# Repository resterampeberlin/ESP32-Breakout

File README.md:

# Purpose

# Credits

This open source code project is has been proudfully produced in Berlin (and other places around the globe) by

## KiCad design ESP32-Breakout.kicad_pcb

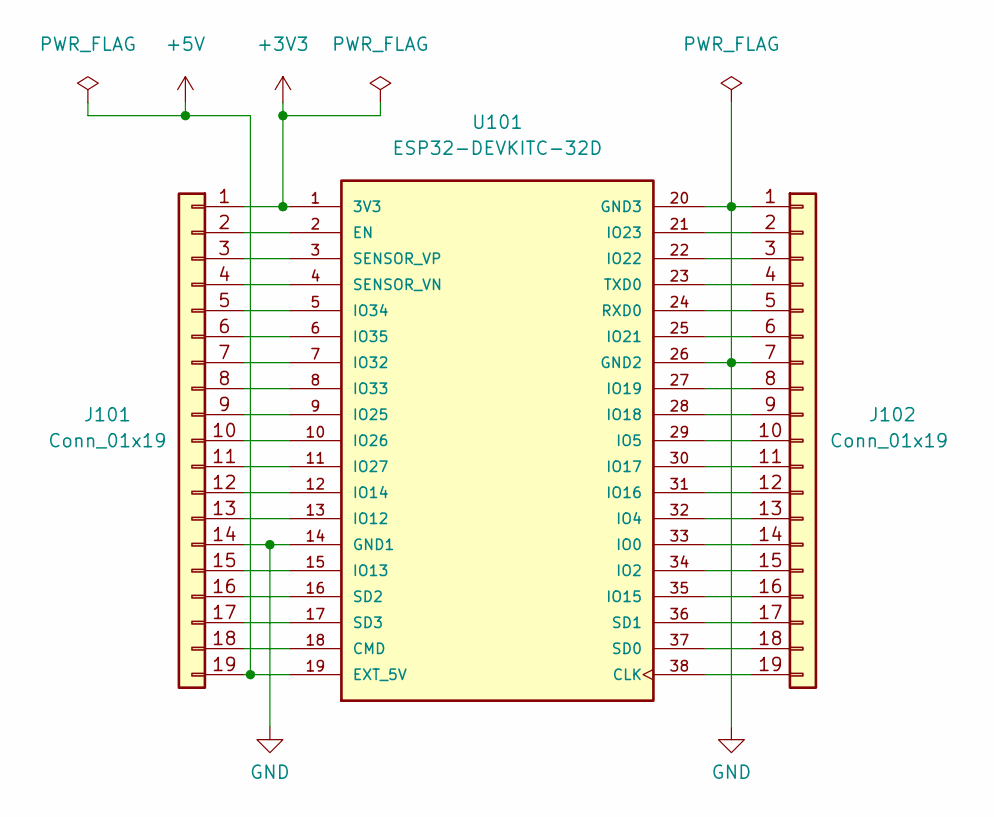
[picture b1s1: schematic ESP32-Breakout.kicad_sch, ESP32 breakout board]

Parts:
J101, J102: Conn_01x19; PinHeader_1x19_P2.54mm_Vertical
U101: ESP32-DEVKITC-32D; MODULE_ESP32-DEVKITC-32D_Stacking_header_TH; PARTREV 4

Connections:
+3V3: J101.1, U101.1 (3V3)
+5V: J101.19, U101.19 (EXT_5V)
GND: J101.14, J102.1, J102.7, U101.14 (GND1), U101.20 (GND3), U101.26 (GND2)
unnamed: J102.2, U101.21 (IO23)
unnamed: J102.3, U101.22 (IO22)
unnamed: J102.4, U101.23 (TXD0)
unnamed: J102.5, U101.24 (RXD0)
unnamed: J102.6, U101.25 (IO21)
unnamed: J102.8, U101.27 (IO19)
unnamed: J102.9, U101.28 (IO18)
unnamed: J102.10, U101.29 (IO5)
unnamed: J102.11, U101.30 (IO17)
unnamed: J102.12, U101.31 (IO16)
unnamed: J102.13, U101.32 (IO4)
unnamed: J102.14, U101.33 (IO0)
unnamed: J102.15, U101.34 (IO2)
unnamed: J102.16, U101.35 (IO15)
unnamed: J102.17, U101.36 (SD1)
unnamed: J102.18, U101.37 (SD0)
unnamed: J102.19, U101.38 (CLK)
unnamed: J101.2, U101.2 (EN)
unnamed: J101.3, U101.3 (SENSOR_VP)
unnamed: J101.4, U101.4 (SENSOR_VN)
unnamed: J101.5, U101.5 (IO34)
unnamed: J101.6, U101.6 (IO35)
unnamed: J101.7, U101.7 (IO32)
unnamed: J101.8, U101.8 (IO33)
unnamed: J101.9, U101.9 (IO25)
unnamed: J101.10, U101.10 (IO26)
unnamed: J101.11, U101.11 (IO27)
unnamed: J101.12, U101.12 (IO14)
unnamed: J101.13, U101.13 (IO12)
unnamed: J101.15, U101.15 (IO13)
unnamed: J101.16, U101.16 (SD2)
unnamed: J101.17, U101.17 (SD3)
unnamed: J101.18, U101.18 (CMD)

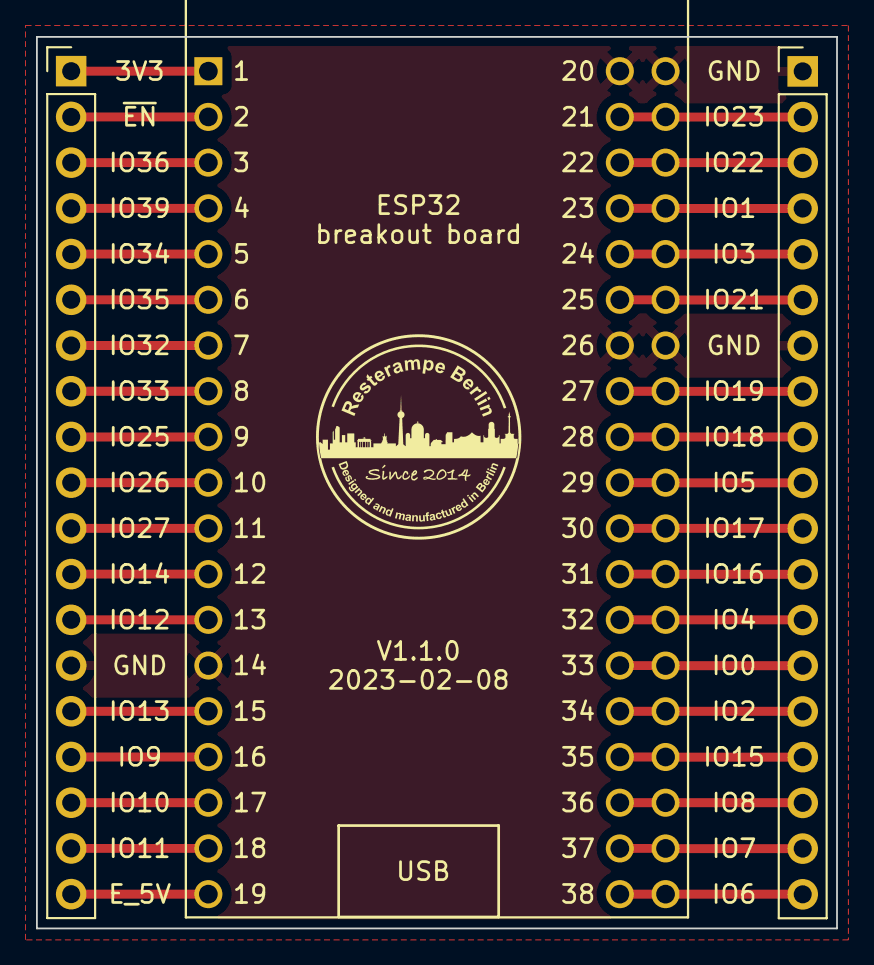
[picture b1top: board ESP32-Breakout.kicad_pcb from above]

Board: 2 copper layers, 44.5 x 49.5 mm, 3 parts (0 on the bottom side), 36 nets.

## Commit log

2023-01-30 Initial version
2023-01-31 Production
2023-01-31 Documentation update, name of board on PCB
2023-02-02 Added 3D stacking header
2023-02-02 Names streamlined
2023-02-08 Closed #1

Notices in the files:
ESP32-Breakout.kicad_pcb:
https://creativecommons.org/licenses/by-nc/4.0
License CC BY-NC 4.0
